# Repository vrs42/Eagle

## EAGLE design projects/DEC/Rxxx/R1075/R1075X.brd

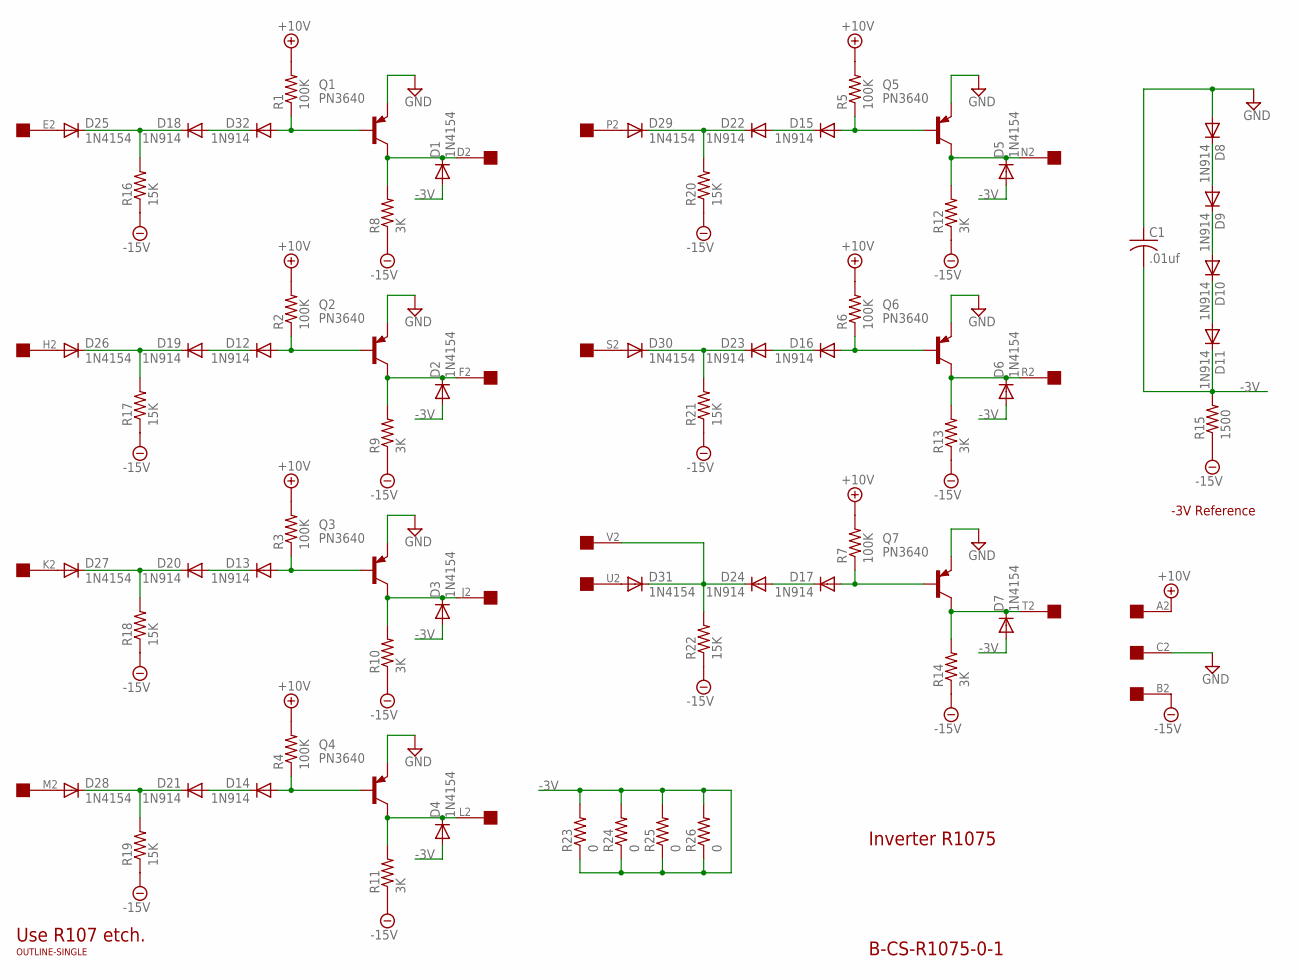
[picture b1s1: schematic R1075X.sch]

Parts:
C1: .01uf; C063-025X075
D1, D2, D3, D4, D5, D6, D7, D25, D26, D27, D28, D29, D30, D31: 1N4154; DO35-10
D8, D9, D10, D11, D12, D13, D14, D15, D16, D17, D18, D19, D20, D21, D22, D23, D24, D32: 1N914; DO35-10
Q1, Q2, Q3, Q4, Q5, Q6, Q7: PN3640; TO39
R1, R2, R3, R4, R5, R6, R7: 100K; 0207/10
R8, R9, R10, R11, R12, R13, R14: 3K; 0207/10
R15: 1500; 0207/10
R16, R17, R18, R19, R20, R21, R22: 15K; 0207/10
R23, R24, R25, R26: 0; 0207/10
U$1: OUTLINE-SINGLE; SINGLE
U$2: EDGE-1; EDGE-CON1

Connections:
+10V: R1.2, R2.2, R3.2, R4.2, R5.2, R6.2, R7.2, U$2.A2
-3V: C1.2, D1.A, D2.A, D3.A, D4.A, D5.A, D6.A, D7.A, D11.C, R15.2, R23.1, R23.2, R24.1, R24.2, R25.1, R25.2, R26.1, R26.2
-15V: R8.1, R9.1, R10.1, R11.1, R12.1, R13.1, R14.1, R15.1, R16.1, R17.1, R18.1, R19.1, R20.1, R21.1, R22.1, U$2.B2
GND: C1.1, D8.A, Q1.1 (E), Q2.1 (E), Q3.1 (E), Q4.1 (E), Q5.1 (E), Q6.1 (E), Q7.1 (E), U$2.C2
unnamed: D7.C, Q7.3 (C), R14.2, U$2.T2
unnamed: D12.A, Q2.2 (B), R2.1
unnamed: D8.C, D9.A
unnamed: D2.C, Q2.3 (C), R9.2, U$2.F2
unnamed: D26.A, U$2.H2
unnamed: D19.C, D26.C, R17.2
unnamed: D12.C, D19.A
unnamed: D13.A, Q3.2 (B), R3.1
unnamed: D3.C, Q3.3 (C), R10.2, U$2.J2
unnamed: D27.A, U$2.K2
unnamed: D20.C, D27.C, R18.2
unnamed: D13.C, D20.A
unnamed: D9.C, D10.A
unnamed: D31.A, U$2.U2
unnamed: D17.A, Q7.2 (B), R7.1
unnamed: D10.C, D11.A
unnamed: D24.C, D31.C, R22.2, U$2.V2
unnamed: D17.C, D24.A
unnamed: D32.A, Q1.2 (B), R1.1
unnamed: D1.C, Q1.3 (C), R8.2, U$2.D2
unnamed: D25.A, U$2.E2
unnamed: D18.C, D25.C, R16.2
unnamed: D18.A, D32.C
unnamed: D14.A, Q4.2 (B), R4.1
unnamed: D4.C, Q4.3 (C), R11.2, U$2.L2
unnamed: D28.A, U$2.M2
unnamed: D21.C, D28.C, R19.2
unnamed: D14.C, D21.A
unnamed: D15.A, Q5.2 (B), R5.1
unnamed: D5.C, Q5.3 (C), R12.2, U$2.N2
unnamed: D29.A, U$2.P2
unnamed: D22.C, D29.C, R20.2
unnamed: D15.C, D22.A
unnamed: D16.A, Q6.2 (B), R6.1
unnamed: D6.C, Q6.3 (C), R13.2, U$2.R2
unnamed: D30.A, U$2.S2
unnamed: D23.C, D30.C, R21.2
unnamed: D16.C, D23.A

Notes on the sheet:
Inverter R1075
B-CS-R1075-0-1
-3V Reference
Use R107 etch.

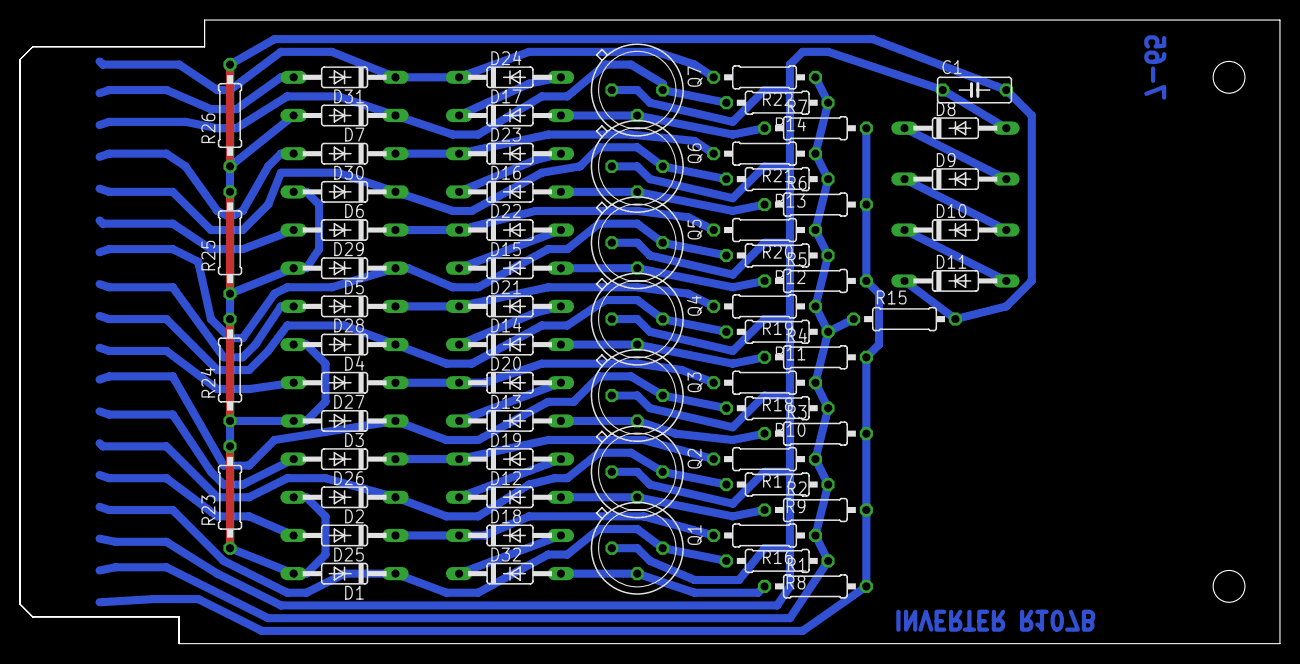
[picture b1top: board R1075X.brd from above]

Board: 2 copper layers, 125.7 x 62.2 mm, 68 parts (0 on the bottom side), 42 nets.

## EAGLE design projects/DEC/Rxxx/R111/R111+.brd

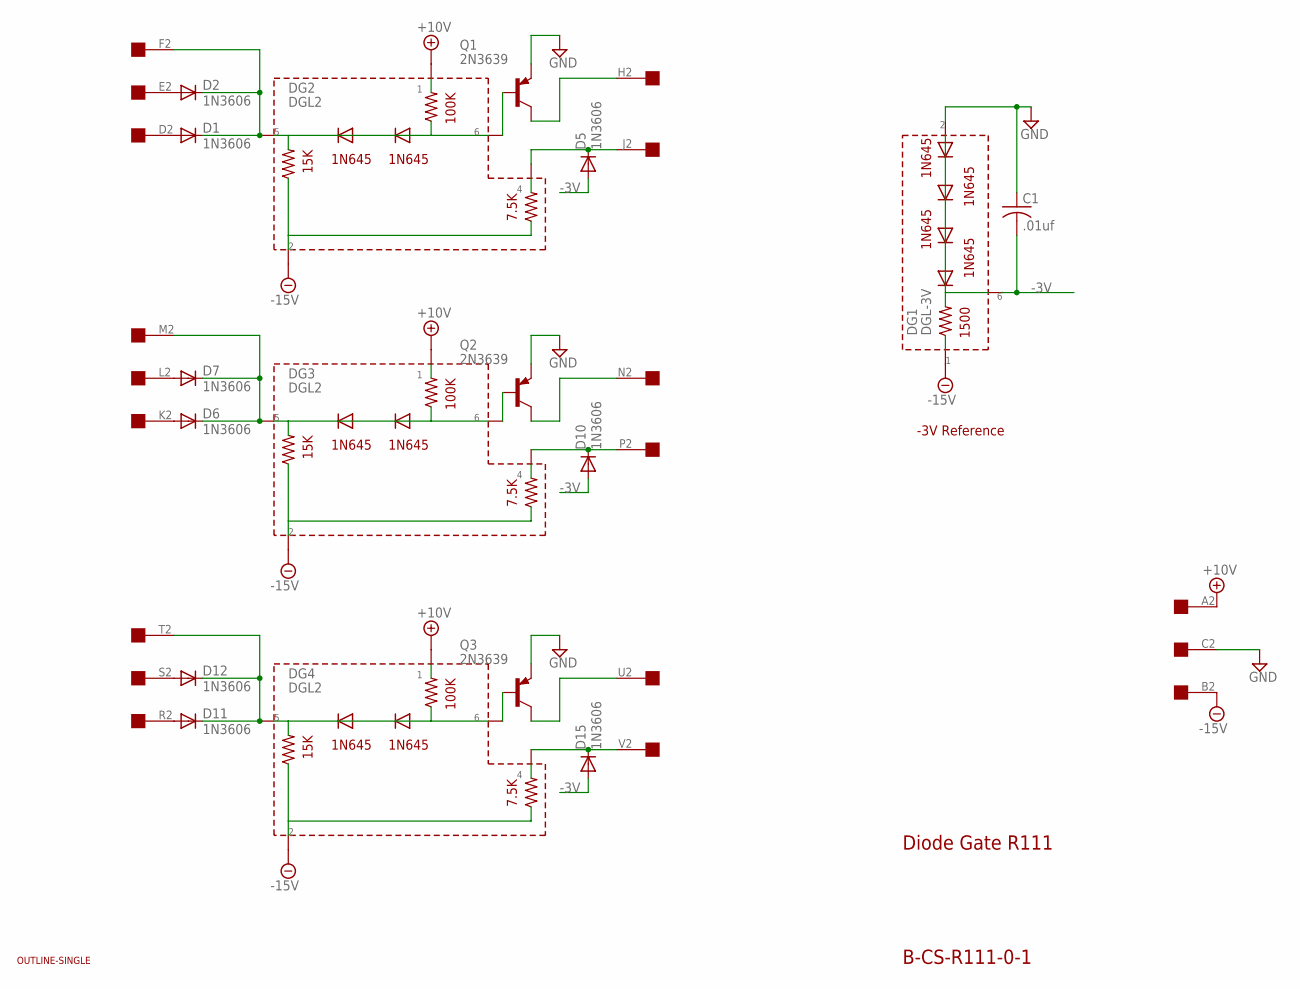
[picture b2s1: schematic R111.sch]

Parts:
C1: .01uf; C050-025X075
D1, D2, D5, D6, D7, D10, D11, D12, D15: 1N3606; DO35-10
DG1: DGL-3V; DGL2
DG2, DG3, DG4: DGL2
Q1, Q2, Q3: 2N3639; TO39
U$1: OUTLINE-SINGLE; SINGLE
U$2: EDGE-1; EDGE-CON1

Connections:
+10V: DG2.P$1 (1), DG3.P$1 (1), DG4.P$1 (1), U$2.A2
-3V: C1.2, D5.A, D10.A, D15.A, DG1.P$6 (6)
-15V: DG1.P$1 (1), DG2.P$2 (2), DG3.P$2 (2), DG4.P$2 (2), U$2.B2
GND: C1.1, DG1.P$2 (2), Q1.1 (E), Q2.1 (E), Q3.1 (E), U$2.C2
unnamed: D6.A, U$2.K2
unnamed: DG2.P$6 (6), Q1.2 (B)
unnamed: D10.C, DG3.P$4 (4), U$2.P2
unnamed: Q1.3 (C), U$2.H2
unnamed: D6.C, D7.C, DG3.P$5 (5), U$2.M2
unnamed: DG3.P$6 (6), Q2.2 (B)
unnamed: DG4.P$6 (6), Q3.2 (B)
unnamed: D15.C, DG4.P$4 (4), U$2.V2
unnamed: D11.A, U$2.R2
unnamed: D11.C, D12.C, DG4.P$5 (5), U$2.T2
unnamed: D7.A, U$2.L2
unnamed: Q2.3 (C), U$2.N2
unnamed: Q3.3 (C), U$2.U2
unnamed: D5.C, DG2.P$4 (4), U$2.J2
unnamed: D1.A, U$2.D2
unnamed: D1.C, D2.C, DG2.P$5 (5), U$2.F2
unnamed: D12.A, U$2.S2
unnamed: D2.A, U$2.E2

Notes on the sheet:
Diode Gate R111
B-CS-R111-0-1
-3V Reference

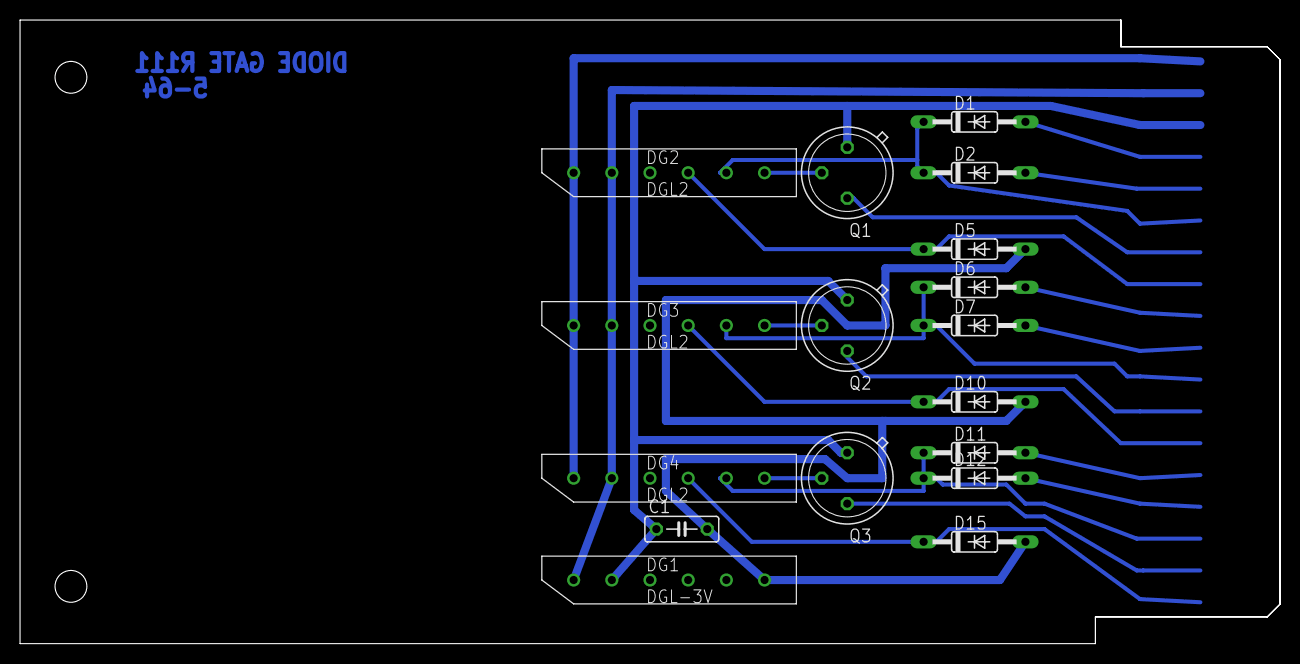
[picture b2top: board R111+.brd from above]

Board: 2 copper layers, 125.7 x 62.2 mm, 19 parts (0 on the bottom side), 22 nets.

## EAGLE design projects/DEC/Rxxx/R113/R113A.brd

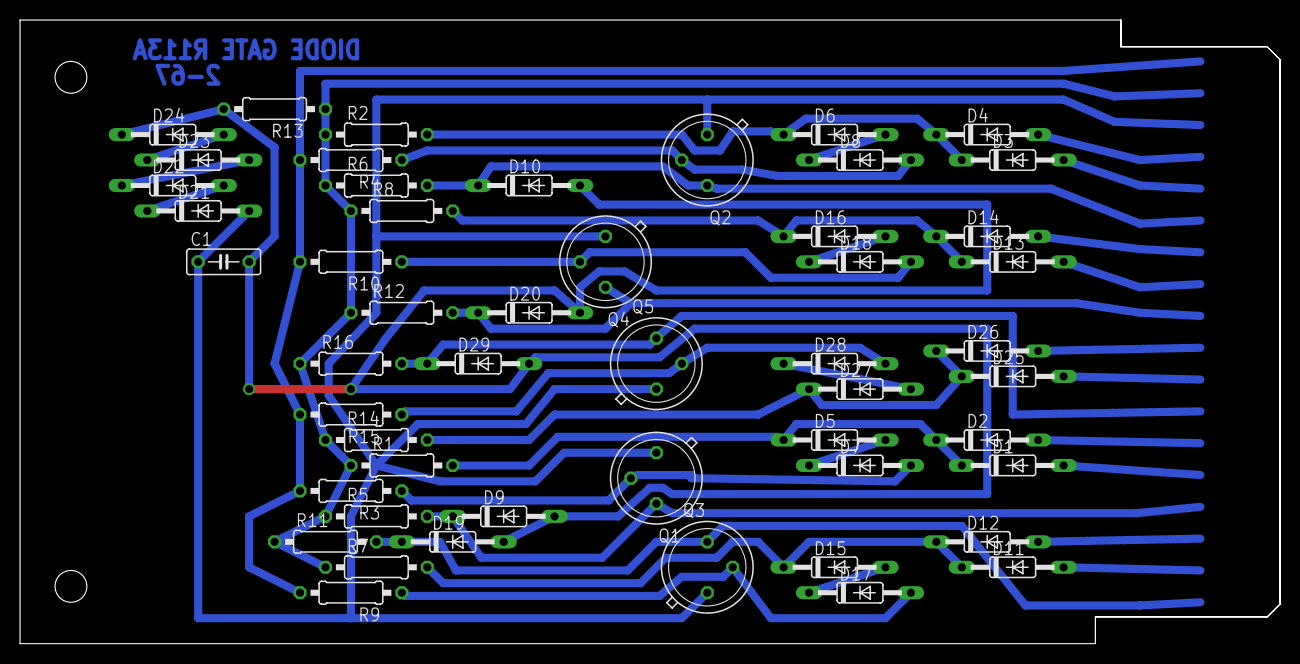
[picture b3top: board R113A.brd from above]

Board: 2 copper layers, 125.7 x 62.2 mm, 53 parts (0 on the bottom side), 37 nets.

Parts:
C1: .01uf; C050-025X075
D1, D2, D3, D4, D9, D10, D11, D12, D13, D14, D19, D20, D25, D26, D29: 1N3606; DO35-10
D5, D6, D7, D8, D15, D16, D17, D18, D21, D22, D23, D24, D27, D28: 1N645; DO35-10
Q1, Q2, Q3, Q4, Q5: 2N3639; TO39
R1, R2, R7, R8, R14: 15K; 0207/10
R3, R4, R9, R10, R15: 100K; 0207/10
R5, R6, R11, R12, R16: 7.5K; 0207/10
R13: 1500; 0207/10
U$1: OUTLINE-SINGLE; SINGLE
U$2: EDGE-1; EDGE-CON1

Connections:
+10V: R3.2, R4.2, R9.2, R10.2, R15.2, U$2.A2
-3V: C1.2, D9.A, D10.A, D19.A, D20.A, D24.C, D29.A, R13.2
-15V: R1.1, R2.1, R5.1, R6.1, R7.1, R8.1, R11.1, R12.1, R13.1, R14.1, R16.1, U$2.B2
GND: C1.1, D21.A, Q1.1, Q2.1, Q3.1, Q4.1, Q5.1, U$2.C2
unnamed: D14.A, U$2.H2
unnamed: D18.A, Q4.2, R10.1
unnamed: D21.C, D22.A
unnamed: D20.C, Q4.3, R12.2, U$2.K2
unnamed: D11.A, U$2.U2
unnamed: D13.C, D14.C, D16.C, R8.2
unnamed: D16.A, D18.C
unnamed: D28.A, Q5.2, R15.1
unnamed: D29.C, Q5.3, R16.2, U$2.N2
unnamed: D26.A, U$2.L2
unnamed: D25.C, D26.C, D27.C, R14.2
unnamed: D27.A, D28.C
unnamed: D22.C, D23.A
unnamed: D13.A, U$2.J2
unnamed: D7.A, Q1.2, R3.1
unnamed: D23.C, D24.A
unnamed: D9.C, Q1.3, R5.2, U$2.S2
unnamed: D2.A, U$2.P2
unnamed: D8.A, Q2.2, R4.1
unnamed: D10.C, Q2.3, R6.2, U$2.F2
unnamed: D4.A, U$2.D2
unnamed: D3.C, D4.C, D6.C, R2.2
unnamed: D6.A, D8.C
unnamed: D1.C, D2.C, D5.C, R1.2
unnamed: D5.A, D7.C
unnamed: D17.A, Q3.2, R9.1
unnamed: D11.C, D12.C, D15.C, R7.2
unnamed: D15.A, D17.C
unnamed: D1.A, U$2.R2
unnamed: D12.A, U$2.T2
unnamed: D25.A, U$2.M2
unnamed: D19.C, Q3.3, R11.2, U$2.V2
unnamed: D3.A, U$2.E2
